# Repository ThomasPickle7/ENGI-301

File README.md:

<h1>ENGI 301 </h1>
Repository for ENGI 301 Coursework
Includes classes made for class as well as those necessary for the Fall 2023 midterm project
RELEVANT MODULES:
AHT10
MPU6050
SSD1306
pedometer
watch
smart_watch

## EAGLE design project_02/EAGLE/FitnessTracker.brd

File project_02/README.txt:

This is the PCB Layout for FitnessTracker. The PCB incorporates a 128x32 OLED screen, for which there is ample space on the board, as well as a gyroscope and weather sensor. 
The tracker has three buttons:
MODE: Changes between time mode, which tells the time, and tracking mode, which displays the steps tracked by the watch as well as the ambient temperature and humidity.
SET: Increments either the hours or minutes of the watch depending on which is selected
TOGGLE: toggles between the minutes and hours so that either can be incremented.
All processing on the FitnessTracker is done on the PocketBeagle, which is mounted with micro-USB facing out from the board.

NOTE- BOM was formatting strangely when i tried to delete fiduciaries/mounting holes, so I manually typed it as well as submitted the raw BOM and added descriptions to the manually typed one. The one EAGLE Generated is labeled 'FitnessTracker BOM (GENERATED).csv'. Thank you and Merry Christmas

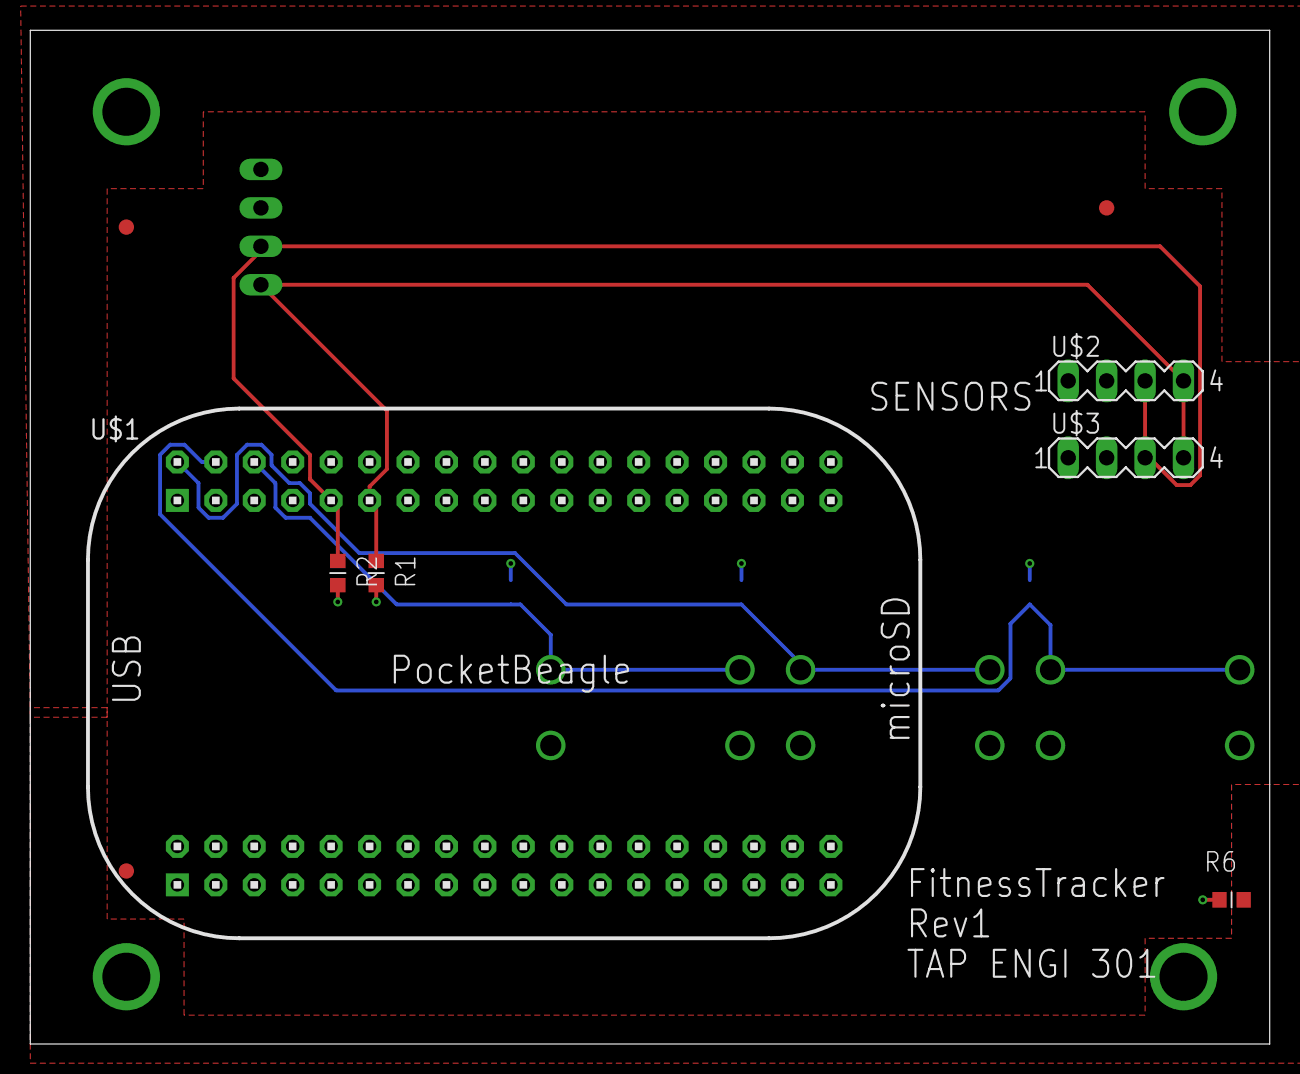
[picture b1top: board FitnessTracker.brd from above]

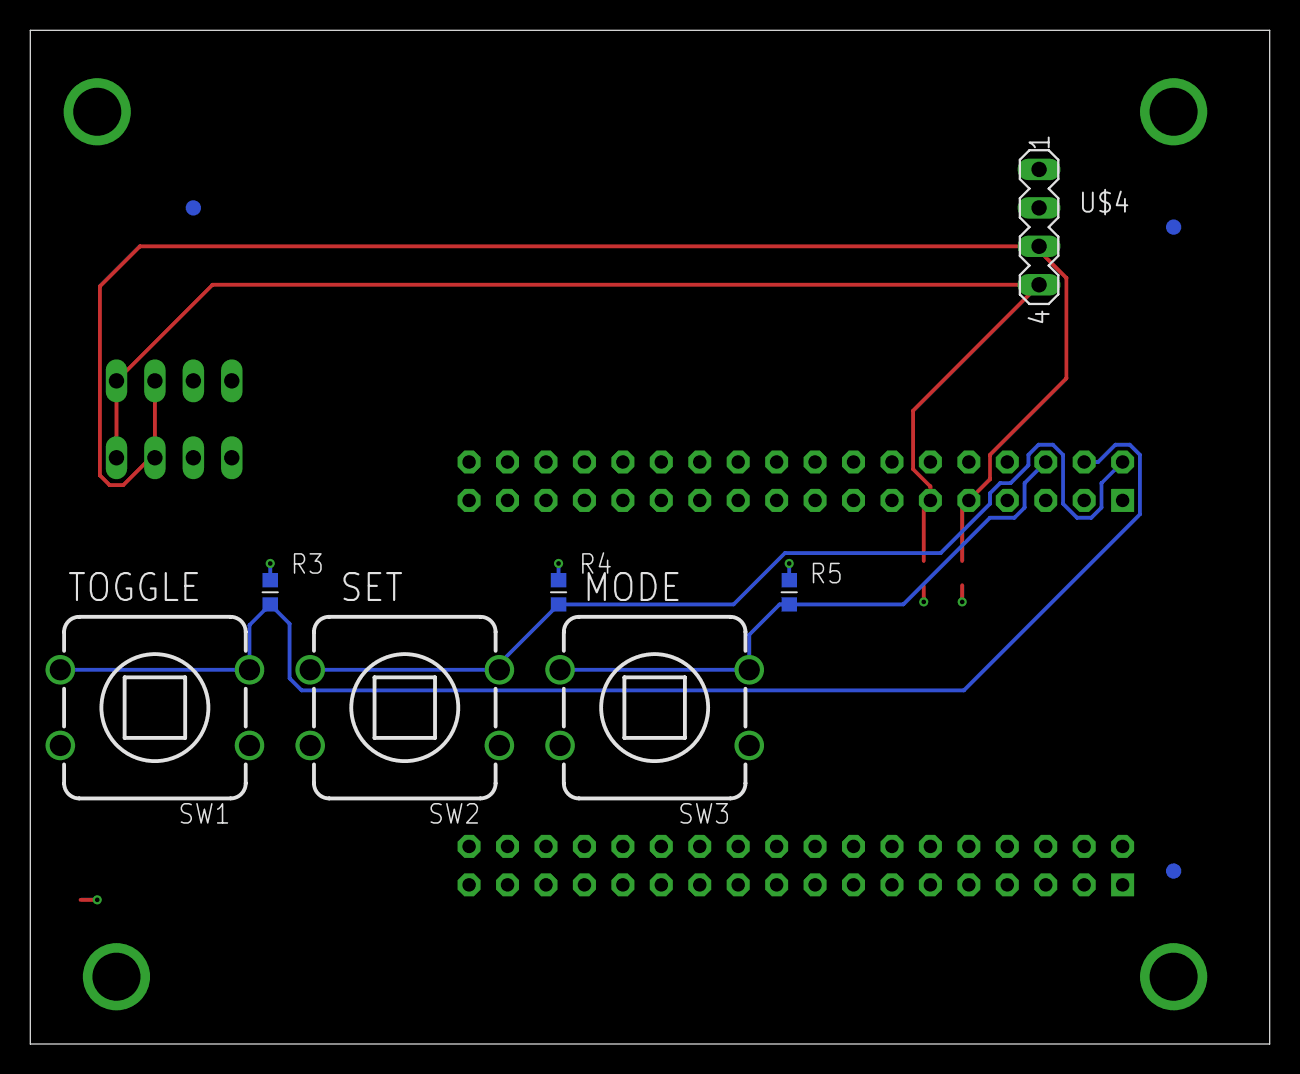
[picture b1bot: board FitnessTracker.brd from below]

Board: 4 copper layers, 81.9 x 67.0 mm, 23 parts (10 on the bottom side), 8 nets.

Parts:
FUD1, FUD2, FUD3, FUD4, FUD5, FUD6: FIDUCIAL; FIDUCIAL_40MIL
MGT1, MGT2, MGT3, MGT4: MOUNTING_HOLE
R1, R2, R3, R4, R5: 1K; R0603
R6: 1M; R0603
SW1, SW2, SW3: PUSH_BUTTON; BUTTON_12.5MM
U$1: POCKETBEAGLE
U$2: SSD1306; MA04-1
U$3: MPU6050; MA04-1
U$4: AHT10; MA04-1

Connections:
CGND: MGT1.P$1, MGT2.P$1, MGT3.P$1, MGT4.P$1, R6.2
GND: R6.1, SW1.1, SW1.3, SW2.1, SW2.3, SW3.1, SW3.3, U$1.21@P2, U$2.1, U$3.2, U$4.2
I2C_SCL: R2.1, U$1.9@P2, U$2.3, U$3.3, U$4.3
I2C_SDA: R1.1, U$1.11@P2, U$2.4, U$3.4, U$4.4
MODE_BUTTON: R5.1, SW3.2, SW3.4, U$1.6@P2
SET_BUTTON: R4.1, SW2.2, SW2.4, U$1.2@P2
TOGGLE_BUTTON: R3.1, SW1.2, SW1.4, U$1.4@P2
VDD_3P3V: R1.2, R2.2, R3.2, R4.2, R5.2, U$1.23@P2, U$2.2, U$3.1, U$4.1

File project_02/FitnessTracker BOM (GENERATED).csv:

"Part";"Value";"Device";"Package";"Description";"";
"FUD1";"FIDUCIAL";"FIDUCIAL";"FIDUCIAL_40MIL";"";"";
"FUD2";"FIDUCIAL";"FIDUCIAL";"FIDUCIAL_40MIL";"";"";
"FUD3";"FIDUCIAL";"FIDUCIAL";"FIDUCIAL_40MIL";"";"";
"FUD4";"FIDUCIAL";"FIDUCIAL";"FIDUCIAL_40MIL";"";"";
"FUD5";"FIDUCIAL";"FIDUCIAL";"FIDUCIAL_40MIL";"";"";
"FUD6";"FIDUCIAL";"FIDUCIAL";"FIDUCIAL_40MIL";"";"";
"MGT1";"MOUNTING_HOLE";"MOUNTING_HOLE";"MOUNTING_HOLE";"Chassis Mounting Hole w/GND connection ability";"";
"MGT2";"MOUNTING_HOLE";"MOUNTING_HOLE";"MOUNTING_HOLE";"Chassis Mounting Hole w/GND connection ability";"";
"MGT3";"MOUNTING_HOLE";"MOUNTING_HOLE";"MOUNTING_HOLE";"Chassis Mounting Hole w/GND connection ability";"";
"MGT4";"MOUNTING_HOLE";"MOUNTING_HOLE";"MOUNTING_HOLE";"Chassis Mounting Hole w/GND connection ability";"";
"R1";"1K";"R_R0603";"R0603";"RESISTOR, American symbol";"";
"R2";"1K";"R_R0603";"R0603";"RESISTOR, American symbol";"";
"R3";"1K";"R_R0603";"R0603";"RESISTOR, American symbol";"";
"R4";"1K";"R_R0603";"R0603";"RESISTOR, American symbol";"";
"R5";"1K";"R_R0603";"R0603";"RESISTOR, American symbol";"";
"R6";"1M";"R_R0603";"R0603";"RESISTOR, American symbol";"";
"SW1";"PUSH_BUTTON";"PUSH_BUTTON";"BUTTON_12.5MM";"";"";
"SW2";"PUSH_BUTTON";"PUSH_BUTTON";"BUTTON_12.5MM";"";"";
"SW3";"PUSH_BUTTON";"PUSH_BUTTON";"BUTTON_12.5MM";"";"";
"U$1";"POCKETBEAGLE";"POCKETBEAGLE";"POCKETBEAGLE";"";"";
"U$2";"SSD1306";"SSD1306";"MA04-1";"";"";
"U$3";"MPU6050";"MPU6050";"MA04-1";"";"";
"U$4";"AHT10";"AHT10";"MA04-1";"";"";

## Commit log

2023-09-12 This is my first commit to ENGI 301
2023-09-27 This commit implements a simple calculator
2023-09-27 Implemented the blink code for HW4
2023-09-27 added documentation/comments
2023-09-27 Implemented button.py code
2023-09-29 new stuff
2023-09-29 test folder added
2023-10-02 fixed button code
2023-10-04 updated my code!
2023-10-04 fixed button code and added people counter
2023-10-06 implements the LED code
2023-10-20 added combo lock code
2023-10-24 began/added stopwatch function
2023-11-08 Added code for Sensors and OLED Display
2023-11-09 Implemented humidity sensor and gyro classes
2023-11-14 updated my code for sensors and upper level modules
2023-11-14 implemented programmable clock
2023-11-14 Create smartwatch
2023-11-14 Create pedometer
2023-11-14 implemented pedometer code
2023-11-15 implemented a smart watch
2023-11-15 Update AHT10.py
    added comments
2023-11-15 Update MPU6050.py
    added comments
2023-12-13 Imported project 2
2023-12-13 Final touches to project 2
2023-12-13 Added Mechanical Drawing
2023-12-13 Imported Machine Screenshots
2023-12-17 moved project files to dedicated folder
2023-12-17 Moved fiels to adequate folder
